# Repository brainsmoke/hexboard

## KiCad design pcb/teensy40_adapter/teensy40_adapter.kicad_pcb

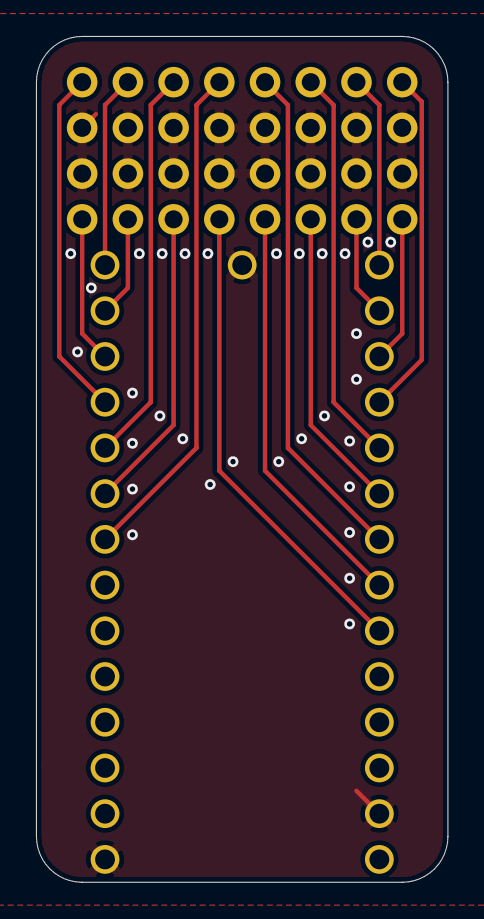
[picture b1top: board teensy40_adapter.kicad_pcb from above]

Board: 2 copper layers, 22.9 x 47.0 mm, 3 parts (1 on the bottom side), 17 nets.

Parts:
J1, J2: Conn_02x08_Odd_Even; PinHeader_2x08_P2.54mm_Vertical
U1: Teensy4.0; Teensy40

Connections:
GND: J1.2, J1.4, J1.6, J1.8, J1.10, J1.12, J1.14, J1.16, J2.2, J2.4, J2.6, J2.8, J2.10, J2.12, J2.14, J2.16, U1.1, U1.17, U1.32
P0: J2.1, U1.23
P1: J2.3, U1.20
P2: J2.5, U1.24
P3: J2.7, U1.26
P4: J2.9, U1.8
P5: J2.11, U1.10
P6: J2.13, U1.14
P7: J2.15, U1.11
P8: J1.1, U1.12
P9: J1.3, U1.13
P10: J1.5, U1.9
P11: J1.7, U1.28
P12: J1.9, U1.27
P13: J1.11, U1.25
P14: J1.13, U1.21
P15: J1.15, U1.22

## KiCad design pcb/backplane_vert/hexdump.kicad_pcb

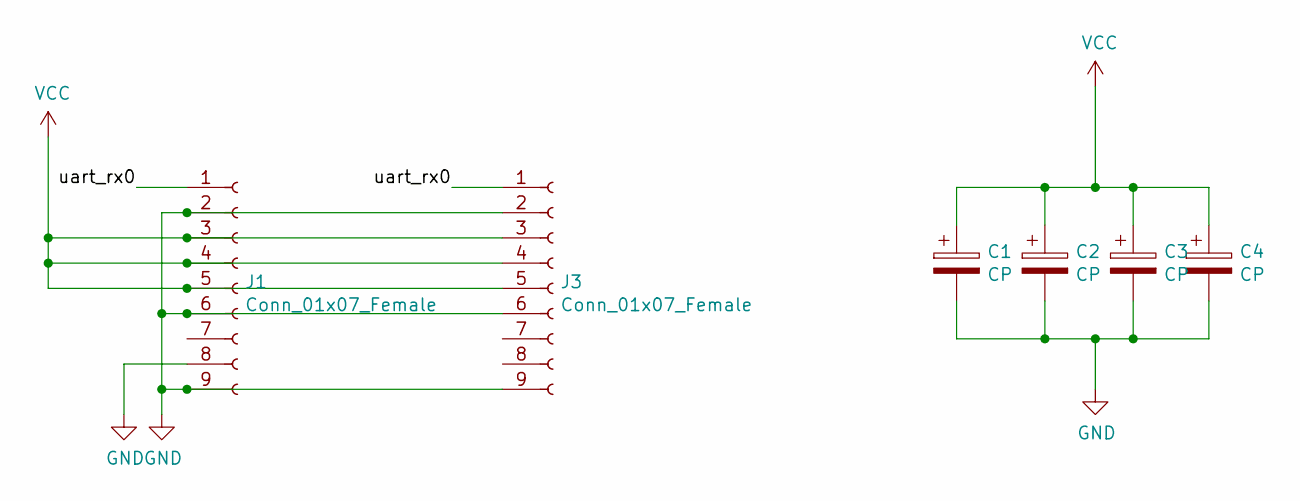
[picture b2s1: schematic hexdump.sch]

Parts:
C1: CP; CP_Elec_10x10
C2: CP; CP_Elec_8x6.9
C3: CP; C_Radial_D10.0mm_H16.0mm_P5.00mm
C4: CP; C_Radial_D8.0mm_H11.5mm_P3.50mm
J1, J3: Conn_01x07_Female; header-1x9

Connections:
/uart_rx0: J1.1, J3.1
GND: C1.2, C2.2, C3.2, C4.2, J1.2, J1.6, J1.8, J1.9, J3.2, J3.6, J3.9
VCC: C1.1, C2.1, C3.1, C4.1, J1.3, J1.4, J1.5, J3.3, J3.4, J3.5

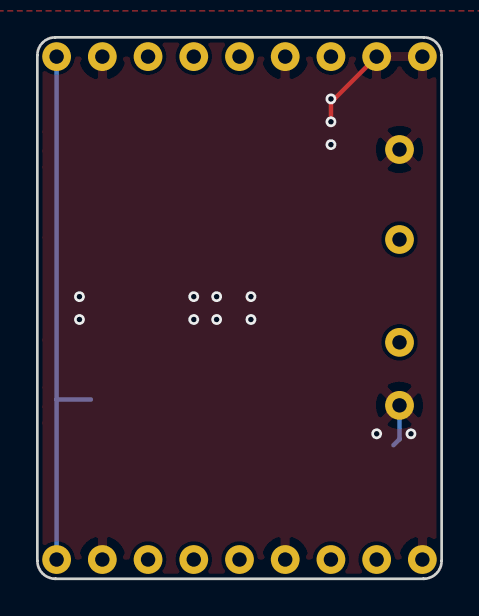
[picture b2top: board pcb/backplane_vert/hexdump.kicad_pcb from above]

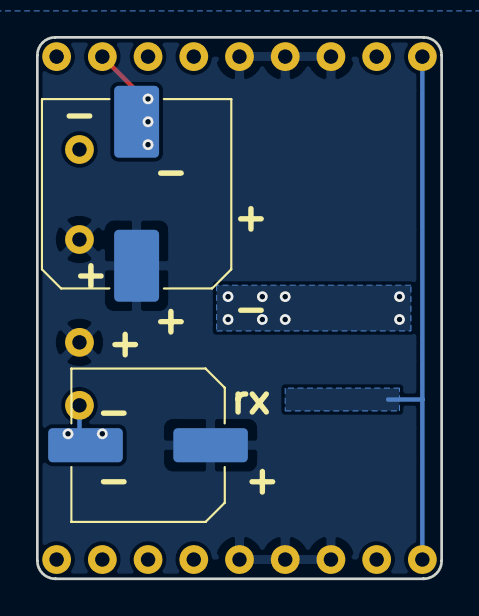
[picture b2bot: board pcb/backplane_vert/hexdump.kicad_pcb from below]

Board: 2 copper layers, 22.5 x 30.1 mm, 6 parts (3 on the bottom side), 3 nets.

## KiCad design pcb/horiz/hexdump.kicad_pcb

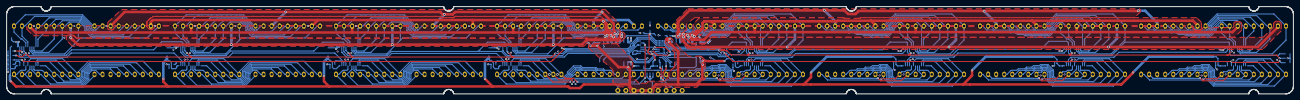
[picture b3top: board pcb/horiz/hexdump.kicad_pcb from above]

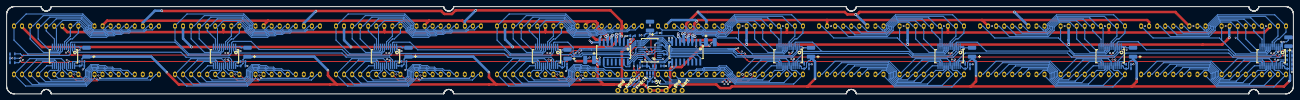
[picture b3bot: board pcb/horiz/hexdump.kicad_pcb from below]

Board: 4 copper layers, 406.0 x 27.5 mm, 70 parts (53 on the bottom side), 158 nets.

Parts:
C1, C2, C3, C4, C5, C6, C7, C8, C9, C10, C11, C12, C13, C25: C; C0603
C14, C15, C16, C17, C18, C19, C20, C21, C22, C23, C24: C; C1210_polar
IC1: STM32F030F4; tssop20
J1: Conn_01x07_Female; header-1x7
JP1: SolderJumper_2_Bridged; JMP0603
R1, R2, R3, R4, R5, R6, R7, R8, R9, R10, R11, R12, R13, R14, R15: R; R0603
U1, U4, U7, U10, U13, U16, U19, U22: ICN3038; SSOP-24_3.9x8.7mm_P0.635mm
U2, U3, U5, U6, U8, U9, U11, U12, U14, U15, U17, U18, U20, U21, U23, U24: Houkem-5421-BSG; 2-digit 14 segment display 25.2x21 mm
U25, U26: TC7258E; SOP-16-1.27mm
U27: AP2204K-3.3; SOT-23-5

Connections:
/2x2digit 14 segment/A: U1.8, U2.12, U3.12
/2x2digit 14 segment/B: U1.7, U2.10, U3.10
/2x2digit 14 segment/C: U1.19, U2.9, U3.9
/2x2digit 14 segment/D: U1.14, U2.7, U3.7
/2x2digit 14 segment/Dp: U1.15, U2.8, U3.8
/2x2digit 14 segment/E: U1.20, U2.1, U3.1
/2x2digit 14 segment/F: U1.5, U2.18, U3.18
/2x2digit 14 segment/G1: U1.9, U2.13, U3.13
/2x2digit 14 segment/G2: U1.13, U2.6, U3.6
/2x2digit 14 segment/H: U1.6, U2.17, U3.17
/2x2digit 14 segment/J: U1.10, U2.15, U3.15
/2x2digit 14 segment/K: U1.11, U2.14, U3.14
/2x2digit 14 segment/L: U1.16, U2.5, U3.5
/2x2digit 14 segment/M: U1.17, U2.4, U3.4
/2x2digit 14 segment/N: U1.18, U2.2, U3.2
/3V3: C10.1, C11.1, C16.1, C25.1, IC1.4, IC1.5, IC1.16, JP1.1, JP1.2, R15.2, U27.5
/!oe: IC1.12, R10.1, R13.1, U1.21, U4.21, U7.21, U10.21, U13.21, U16.21, U19.21, U22.21
/A_select: IC1.18, U25.15, U26.15
/B_select: IC1.17, U25.16, U26.16
/DIG0N: U14.16, U17.16, U20.16, U23.16, U26.3
/DIG0S: U2.16, U5.16, U8.16, U11.16, U25.3
/DIG1N: U14.11, U17.11, U20.11, U23.11, U26.6
/DIG1S: U2.11, U5.11, U8.11, U11.11, U25.6
/DIG2N: U15.16, U18.16, U21.16, U24.16, U26.5
/DIG2S: U3.16, U6.16, U9.16, U12.16, U25.5
/DIG3N: U15.11, U18.11, U21.11, U24.11, U26.4
/DIG3S: U3.11, U6.11, U9.11, U12.11, U25.4
/ENH: IC1.11, U25.7, U26.7
/ENL: IC1.14, R15.1, U25.10, U26.10
/clk_north: IC1.8, R12.1, U13.3, U16.3, U19.3, U22.3
/clk_south: IC1.7, R9.1, U1.3, U4.3, U7.3, U10.3
/data_north: IC1.10, U13.2
/data_south: IC1.6, U1.2
/le: IC1.13, R11.1, R14.1, U1.4, U4.4, U7.4, U10.4, U13.4, U16.4, U19.4, U22.4
/sheet5D3BEBE4/A: U4.8, U5.12, U6.12
/sheet5D3BEBE4/B: U4.7, U5.10, U6.10
/sheet5D3BEBE4/C: U4.19, U5.9, U6.9
/sheet5D3BEBE4/D: U4.14, U5.7, U6.7
/sheet5D3BEBE4/DI: U1.22, U4.2
/sheet5D3BEBE4/Dp: U4.15, U5.8, U6.8
/sheet5D3BEBE4/E: U4.20, U5.1, U6.1
/sheet5D3BEBE4/F: U4.5, U5.18, U6.18
/sheet5D3BEBE4/G1: U4.9, U5.13, U6.13
/sheet5D3BEBE4/G2: U4.13, U5.6, U6.6
/sheet5D3BEBE4/H: U4.6, U5.17, U6.17
/sheet5D3BEBE4/J: U4.10, U5.15, U6.15
/sheet5D3BEBE4/K: U4.11, U5.14, U6.14
/sheet5D3BEBE4/L: U4.16, U5.5, U6.5
/sheet5D3BEBE4/M: U4.17, U5.4, U6.4
/sheet5D3BEBE4/N: U4.18, U5.2, U6.2
/sheet5D3BEDDC/A: U7.8, U8.12, U9.12
/sheet5D3BEDDC/B: U7.7, U8.10, U9.10
/sheet5D3BEDDC/C: U7.19, U8.9, U9.9
/sheet5D3BEDDC/D: U7.14, U8.7, U9.7
/sheet5D3BEDDC/DI: U4.22, U7.2
/sheet5D3BEDDC/Dp: U7.15, U8.8, U9.8
/sheet5D3BEDDC/E: U7.20, U8.1, U9.1
/sheet5D3BEDDC/F: U7.5, U8.18, U9.18
/sheet5D3BEDDC/G1: U7.9, U8.13, U9.13
/sheet5D3BEDDC/G2: U7.13, U8.6, U9.6
/sheet5D3BEDDC/H: U7.6, U8.17, U9.17
/sheet5D3BEDDC/J: U7.10, U8.15, U9.15
/sheet5D3BEDDC/K: U7.11, U8.14, U9.14
/sheet5D3BEDDC/L: U7.16, U8.5, U9.5
/sheet5D3BEDDC/M: U7.17, U8.4, U9.4
/sheet5D3BEDDC/N: U7.18, U8.2, U9.2
/sheet5D3BEDE9/A: U10.8, U11.12, U12.12
/sheet5D3BEDE9/B: U10.7, U11.10, U12.10
/sheet5D3BEDE9/C: U10.19, U11.9, U12.9
/sheet5D3BEDE9/D: U10.14, U11.7, U12.7
/sheet5D3BEDE9/DI: U7.22, U10.2
/sheet5D3BEDE9/Dp: U10.15, U11.8, U12.8
/sheet5D3BEDE9/E: U10.20, U11.1, U12.1
/sheet5D3BEDE9/F: U10.5, U11.18, U12.18
/sheet5D3BEDE9/G1: U10.9, U11.13, U12.13
/sheet5D3BEDE9/G2: U10.13, U11.6, U12.6
/sheet5D3BEDE9/H: U10.6, U11.17, U12.17
/sheet5D3BEDE9/J: U10.10, U11.15, U12.15
/sheet5D3BEDE9/K: U10.11, U11.14, U12.14
/sheet5D3BEDE9/L: U10.16, U11.5, U12.5
/sheet5D3BEDE9/M: U10.17, U11.4, U12.4
/sheet5D3BEDE9/N: U10.18, U11.2, U12.2
/sheet5D86B5CC/A: U13.8, U14.12, U15.12
/sheet5D86B5CC/B: U13.7, U14.10, U15.10
/sheet5D86B5CC/C: U13.19, U14.9, U15.9
/sheet5D86B5CC/D: U13.14, U14.7, U15.7
/sheet5D86B5CC/Dp: U13.15, U14.8, U15.8
/sheet5D86B5CC/E: U13.20, U14.1, U15.1
/sheet5D86B5CC/F: U13.5, U14.18, U15.18
/sheet5D86B5CC/G1: U13.9, U14.13, U15.13
/sheet5D86B5CC/G2: U13.13, U14.6, U15.6
/sheet5D86B5CC/H: U13.6, U14.17, U15.17
/sheet5D86B5CC/J: U13.10, U14.15, U15.15
/sheet5D86B5CC/K: U13.11, U14.14, U15.14
/sheet5D86B5CC/L: U13.16, U14.5, U15.5
/sheet5D86B5CC/M: U13.17, U14.4, U15.4
/sheet5D86B5CC/N: U13.18, U14.2, U15.2
/sheet5D86B5D9/A: U16.8, U17.12, U18.12
/sheet5D86B5D9/B: U16.7, U17.10, U18.10
/sheet5D86B5D9/C: U16.19, U17.9, U18.9
/sheet5D86B5D9/D: U16.14, U17.7, U18.7
/sheet5D86B5D9/DI: U13.22, U16.2
/sheet5D86B5D9/Dp: U16.15, U17.8, U18.8
/sheet5D86B5D9/E: U16.20, U17.1, U18.1
/sheet5D86B5D9/F: U16.5, U17.18, U18.18
/sheet5D86B5D9/G1: U16.9, U17.13, U18.13
/sheet5D86B5D9/G2: U16.13, U17.6, U18.6
/sheet5D86B5D9/H: U16.6, U17.17, U18.17
/sheet5D86B5D9/J: U16.10, U17.15, U18.15
/sheet5D86B5D9/K: U16.11, U17.14, U18.14
/sheet5D86B5D9/L: U16.16, U17.5, U18.5
/sheet5D86B5D9/M: U16.17, U17.4, U18.4
/sheet5D86B5D9/N: U16.18, U17.2, U18.2
/sheet5D86B5F7/A: U19.8, U20.12, U21.12
/sheet5D86B5F7/B: U19.7, U20.10, U21.10
/sheet5D86B5F7/C: U19.19, U20.9, U21.9
/sheet5D86B5F7/D: U19.14, U20.7, U21.7
/sheet5D86B5F7/DI: U16.22, U19.2
/sheet5D86B5F7/Dp: U19.15, U20.8, U21.8
/sheet5D86B5F7/E: U19.20, U20.1, U21.1
/sheet5D86B5F7/F: U19.5, U20.18, U21.18
/sheet5D86B5F7/G1: U19.9, U20.13, U21.13
/sheet5D86B5F7/G2: U19.13, U20.6, U21.6
/sheet5D86B5F7/H: U19.6, U20.17, U21.17
/sheet5D86B5F7/J: U19.10, U20.15, U21.15
/sheet5D86B5F7/K: U19.11, U20.14, U21.14
/sheet5D86B5F7/L: U19.16, U20.5, U21.5
/sheet5D86B5F7/M: U19.17, U20.4, U21.4
/sheet5D86B5F7/N: U19.18, U20.2, U21.2
/sheet5D86B604/A: U22.8, U23.12, U24.12
/sheet5D86B604/B: U22.7, U23.10, U24.10
/sheet5D86B604/C: U22.19, U23.9, U24.9
/sheet5D86B604/D: U22.14, U23.7, U24.7
/sheet5D86B604/DI: U19.22, U22.2
/sheet5D86B604/Dp: U22.15, U23.8, U24.8
/sheet5D86B604/E: U22.20, U23.1, U24.1
/sheet5D86B604/F: U22.5, U23.18, U24.18
/sheet5D86B604/G1: U22.9, U23.13, U24.13
/sheet5D86B604/G2: U22.13, U23.6, U24.6
/sheet5D86B604/H: U22.6, U23.17, U24.17
/sheet5D86B604/J: U22.10, U23.15, U24.15
/sheet5D86B604/K: U22.11, U23.14, U24.14
/sheet5D86B604/L: U22.16, U23.5, U24.5
/sheet5D86B604/M: U22.17, U23.4, U24.4
/sheet5D86B604/N: U22.18, U23.2, U24.2
/swdclk: IC1.20, J1.7
/swdio: IC1.19, J1.8
/uart_rx: IC1.9, J1.1
GND: C1.2, C2.2, C3.2, C4.2, C5.2, C6.2, C7.2, C8.2, C9.2, C10.2, C11.2, C12.2, C13.2, C14.2, C15.2, C16.2, C17.2, C18.2, C19.2, C20.2, C21.2, C22.2, C23.2, C24.2, C25.2, IC1.1, IC1.15, J1.2, J1.6, J1.9, R1.1, R2.1, R3.1, R4.1, R5.1, R6.1, R7.1, R8.1, R9.2, R10.2, R11.2, R12.2, R13.2, R14.2, U1.1, U4.1, U7.1, U10.1, U13.1, U16.1, U19.1, U22.1, U25.2, U25.8, U26.2, U26.8, U27.2
unnamed: R1.2, U1.23
unnamed: R2.2, U4.23
unnamed: R3.2, U7.23
unnamed: R4.2, U10.23
unnamed: R5.2, U13.23
unnamed: R6.2, U16.23
unnamed: R7.2, U19.23
unnamed: R8.2, U22.23
VCC: C1.1, C2.1, C3.1, C4.1, C5.1, C6.1, C7.1, C8.1, C9.1, C12.1, C13.1, C14.1, C15.1, C17.1, C18.1, C19.1, C20.1, C21.1, C22.1, C23.1, C24.1, J1.3, J1.4, J1.5, U1.24, U4.24, U7.24, U10.24, U13.24, U16.24, U19.24, U22.24, U25.1, U25.9, U26.1, U26.9, U27.1, U27.3

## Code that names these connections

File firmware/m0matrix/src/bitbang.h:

#ifndef BITBANG_H
#define BITBANG_H

/* platform constants */

#define GPIO_ODR_OFFSET (0x14)
#define GPIO_BSRR_OFFSET (0x18)

/* protocol */

#define END_OF_FRAME (0xfe)
#define DISCARD_FRAME (0xff)

/* GPIO, BSRR */

#define CLEAR(X) (X<<16)
#define SET(X)   (X)

/* GPIO A */
#define PIN_DATA_SOUTH         (0)
#define PIN_DATA_NORTH         (4)
#define PIN_CLK_SOUTH          (1)
#define PIN_CLK_NORTH          (2)
#define PIN_LATCH              (7)
#define PIN_NOT_OUTPUT_ENABLE  (6)
#define PIN_ENABLE_HIGH        (5)
#define PIN_UART_RX            (3)
#define PIN_SELECT_A          (10)
#define PIN_SELECT_B           (9)

#define BIT_DATA_NORTH         (1<<PIN_DATA_NORTH)
#define BIT_CLK_NORTH          (1<<PIN_CLK_NORTH)
#define BIT_DATA_SOUTH         (1<<PIN_DATA_SOUTH)
#define BIT_CLK_SOUTH          (1<<PIN_CLK_SOUTH)
#define BIT_LATCH              (1<<PIN_LATCH)
#define BIT_NOT_OUTPUT_ENABLE  (1<<PIN_NOT_OUTPUT_ENABLE)
#define BIT_ENABLE_HIGH        (1<<PIN_ENABLE_HIGH)
#define BIT_SELECT_A           (1<<PIN_SELECT_A)
#define BIT_SELECT_B           (1<<PIN_SELECT_B)

#define MASK_CLK (BIT_CLK_NORTH|BIT_CLK_SOUTH)
#define MASK_DATA (BIT_DATA_NORTH|BIT_DATA_SOUTH)

/* GPIOB */

#define PIN_ENABLE_LOW  (1)

#define BIT_ENABLE_LOW  (1<<PIN_ENABLE_LOW)

/* precomputation */

#define X4(bits) (bits*0x01010101)

/* static constants (code changes needed to change this) */

#define N_ROWS               (4) /* code expects power of two */
#define N_CHANNELS           (2)
#define N_CHIPS_PER_CHANNEL  (4)
#define N_PINS_PER_CHIP      (16)

/* derived constants */

#define N_BITS_PER_CHANNEL   (N_CHIPS_PER_CHANNEL*N_PINS_PER_CHIP)
#define N_BITS_PER_ROW       (N_BITS_PER_CHANNEL*N_CHANNELS)
#define N_LEDS               (N_BITS_PER_CHANNEL*N_CHANNELS*N_ROWS)

#ifndef __ASSEMBLER__

#include <stdint.h>

/* sends 64x (max 8) bits parallel at ~1/6th the clockspeed to GPIO[0-7]
 * gpio is the GPIO base address
 * 
 * probably 340 cycles excluding call
 */
void bitbang64_clk_stm32(uint8_t *buffer, volatile uint16_t *gpio);

/* equivalent to:
 *
 * uint8_t *p = precomp_buf;
 * for (i=0; i<128; i+=8)
 *     for (j=0; j<4; j++)
 *         *p++ = bit_set(frame[i+j], bit) * PIN_DATA_NORTH |
 *                bit_set(frame[i+j+4], bit) * PIN_DATA_SOUTH |
 *                nThByteLittleEndian(otherpins4x, j);
 *
 */
void precomp64(uint8_t *precomp_buf, uint8_t *frame, uint32_t bit, uint32_t otherpins4x);

void dithcomp128(uint8_t *residual, uint8_t *frame);

void wait_a_bit(void);

#endif

#endif // BITBANG_H

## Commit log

2019-09-11 The Hexdump
2019-12-18 update PCBs
2019-12-18 add animation software
2019-12-18 add stm32 & teensy firmware
2019-12-18 add readme
2019-12-18 remove commened ou code
2019-12-19 add required teensyduino libs
2020-01-07 decompose ripple animation
2020-01-07 add raindrops animation
2022-09-18 16 bit input
2022-09-30 clean-up 16 bit stm32 code
2022-09-30 add vertical joiner PCB
2022-09-30 add teensy 4.0 adapter
2022-09-30 teensy 4.0 code for parallel synchronous uart tx
2022-10-04 move to 16 bit, 60 fps
2022-10-04 fix all ghosting
2022-10-04 backport code to 8 bit version
2022-10-06 fix animations
2022-10-06 fix pin assignment
2022-10-06 halt MCU for flash operation
2022-10-06 fix cursor position
2022-10-07 cleanup
2022-10-07 fix fps related code, print fps during routine
2022-10-07 improve ripple effect
2022-10-14 refactor
2022-10-16 add small display demo
2022-10-16 add missing halt script
2022-10-16 change ripple
2022-10-16 minor tweak
2022-10-16 add ripple-less cursor
2022-10-16 add arrow key actions
2022-10-25 add fade-out effect (for shutdown)
2022-10-25 add 8x uart code for teensy 3.2
2022-10-25 fix multi-character writes
2022-10-25 fix framebuffer size
2022-10-25 make ripple wave configurable
2022-10-25 change input for test2 demo
2023-10-09 add laser cut case to house a single horizontal bar
